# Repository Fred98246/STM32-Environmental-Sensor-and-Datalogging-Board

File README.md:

# Custom STM32 Environmental Sensor & Datalogging Board

## Project Overview
This repository contains the complete design files and source code for a custom, battery-powered STM32 microcontroller board designed for environmental monitoring and data logging. Measuring at a compact 40 x 58 mm, the board features integrated temperature, humidity, and ambient light sensors, alongside an SD card slot for local data storage. It includes a complete Li-Ion power management system with USB-C charging, load sharing, and battery protection. 

The user interface is driven by a rotary encoder and an external SPI display, making it suitable for standalone automated environments like humidity control or ambient monitoring.

## Repository Structure
*   **Hardware:** Contains the complete KiCad E.D.A. project files, including the schematic and the 4-layer PCB layout.
*   **Manufacturing:** Includes the generated Gerber files, Drill files, and sheets with the Bill of Materials (BOM) required for PCB fabrication and assembly.
*   **Firmware:** Contains the `STM32CubeMX` (`.ioc`) configuration file for peripheral initialization and the C/C++ code with the needed drivers.
*   **docs**: Contains component datasheets and a detailed Bill of Materials (BOM) spreadsheet

## Hardware Implementation Details

### Core Processing
*   **Microcontroller:** The board is powered by the STM32F103C8T6 ARM Cortex-M3 MCU.
*   **Clocking:** A 16MHz crystal oscillator (LFXTAL085871) is implemented to provide the precise clocking required for stable USB communication. 
*   **Debugging/Programming:** Connector for SWD programming, via ST-Link V2.

### Power Management
The power architecture is designed for safe, continuous operation whether plugged in or running on battery:
*   **Battery Charging:** Handled by the MCP73831/2 IC, drawing 5V from the USB-C port to charge a connected Li-Ion cell.
*   **Battery Protection:** An AP9101C IC, paired with dual ZXMN3B14F N-Channel MOSFETs, protects the battery from overcharge, overdischarge, and overcurrent scenarios.
*   **Load Sharing:** An AO3401A P-Channel MOSFET and an SS14 Schottky diode create a seamless load-sharing circuit. This ensures the system runs directly off USB power when plugged in, allowing the battery to charge optimally without system load interference.
*   **Regulation:** An AP2112K-3.3TRG1 LDO provides a stable 3.3V supply for the MCU and logic.

### Sensors & Interfaces
*   **Environmental Sensing:** Utilizes the SHT3x-DIS for high-precision temperature and humidity tracking via I2C.
*   **Light Sensing:** Incorporates the OPT3001DNPRQ1 ambient light sensor, also operating on the I2C bus.
*   **Storage:** A Molex 47219-2001 MicroSD card receptacle is routed via high-speed SPI for data logging in txt file.
*   **Connectivity:** USB-C port configured for USB 2.0 data and power. D3V3XA4B10LP TVS diode arrays are placed on both the USB data lines and the SD card lines to protect against electrostatic discharge (ESD).
*   USB-CDC Virtual COM Port Interface: Integrated full-speed USB communication between the STM32 and host PC, enabling real-time serial telemetry and diagnostic logging for hardware bring-up and physical fault isolation.
*   **User Input:** Hardware debounced rotary encoder footprint with integrated push-button functionality.

## Design Challenges & Signal Integrity
Designing this board within a 40x58mm footprint required careful attention to PCB stackup and signal routing:

*   **Component Footprints & Tolerances:** Extensive review of manufacturer datasheets was required to ensure precise footprint creation and component placement within the restricted 40x58mm board area.
*   **4-Layer Stackup:** To accommodate the component density and maintain strict signal integrity, a 4-layer PCB was utilized (Top Signal, Ground Plane, Power Plane, Bottom Signal). This continuous internal ground plane is critical for providing short return paths for high-frequency signals and minimizing electromagnetic interference (EMI). 
*   **USB Differential Routing:** The USB D+ and D- lines require 90-ohm differential impedance matching. The 4-layer stackup allowed for calculating precise trace widths and spacing over the internal ground plane to hit this impedance target, ensuring reliable USB enumeration and data transfer.
*   **MicroSD SPI Speeds:** Because SD card SPI operates at moderate speeds, it does not require strict impedance matching or length tuning. The 4-layer stackup provided the flexibility to route these signals easily through vias while maintaining a solid ground reference to minimize general EMI.
*   **Mixed-Signal Placement:** Analog sensor lines (I2C for SHT3x and OPT3001) are physically separated from high-speed digital traces (USB, SPI, and the 16MHz crystal) to prevent digital switching noise from coupling into the sensitive environmental readings.
*   **Firmware Architecture:** The C/C++ codebase leverages STM32 HAL libraries, structured with modular driver functions and a streamlined main loop to ensure non-blocking sensor reads and efficient peripheral management.

## Operational Flow & User Interface: 
The firmware is structured around an event-driven state machine that handles user interaction, data logging, and strict power efficiency:

*   **Startup & Menu Navigation:** The system is awakened by a physical press of the rotary encoder. The TFT display initializes and presents an interactive menu where the user can select to view Temperature, Humidity, or Ambient Light.
*   **Active Monitoring:** Upon selection, the screen continuously updates with real-time readings from the designated I2C sensor.
*   **Concurrent Datalogging & Telemetry:** While the system is awake, it automatically mounts the FATFS file system and appends the sensor readings to a `.txt` file on the MicroSD card at strict 10-second intervals. Simultaneously, this data is continuously broadcast over the USB-CDC COM port to a connected PC for live monitoring.
*   **Low-Power Sleep Mode:** To conserve battery, if the system detects no rotary encoder rotation or button clicks for 2 minutes, it automatically gracefully closes the SD card file, powers down the display, and puts the STM32 into a low-power `STOP` state. A subsequent button press triggers an EXTI hardware interrupt, waking the system back to full operation instantly.

## 🚀 Future Scope: Closed-Loop Automation
While currently operating as a standalone datalogger, this board was engineered to serve as the precision sensor node for future automated control systems. By linking the onboard environmental telemetry to external physical actuators (such as fans, humidifiers, or motorized blinds), the hardware will transition into a dynamic closed-loop control environment. 

The high-resolution empirical data currently gathered via the SD card and USB interface provides the foundation for mathematical system identification. This allows the physical environment's behavior to be accurately modeled in software like MATLAB, enabling the future calculation of transfer functions and the implementation of tuned PID or automated sequential control logic directly onto the STM32.

*   **Schematic**:

* **PCB**:

* **3D View**:

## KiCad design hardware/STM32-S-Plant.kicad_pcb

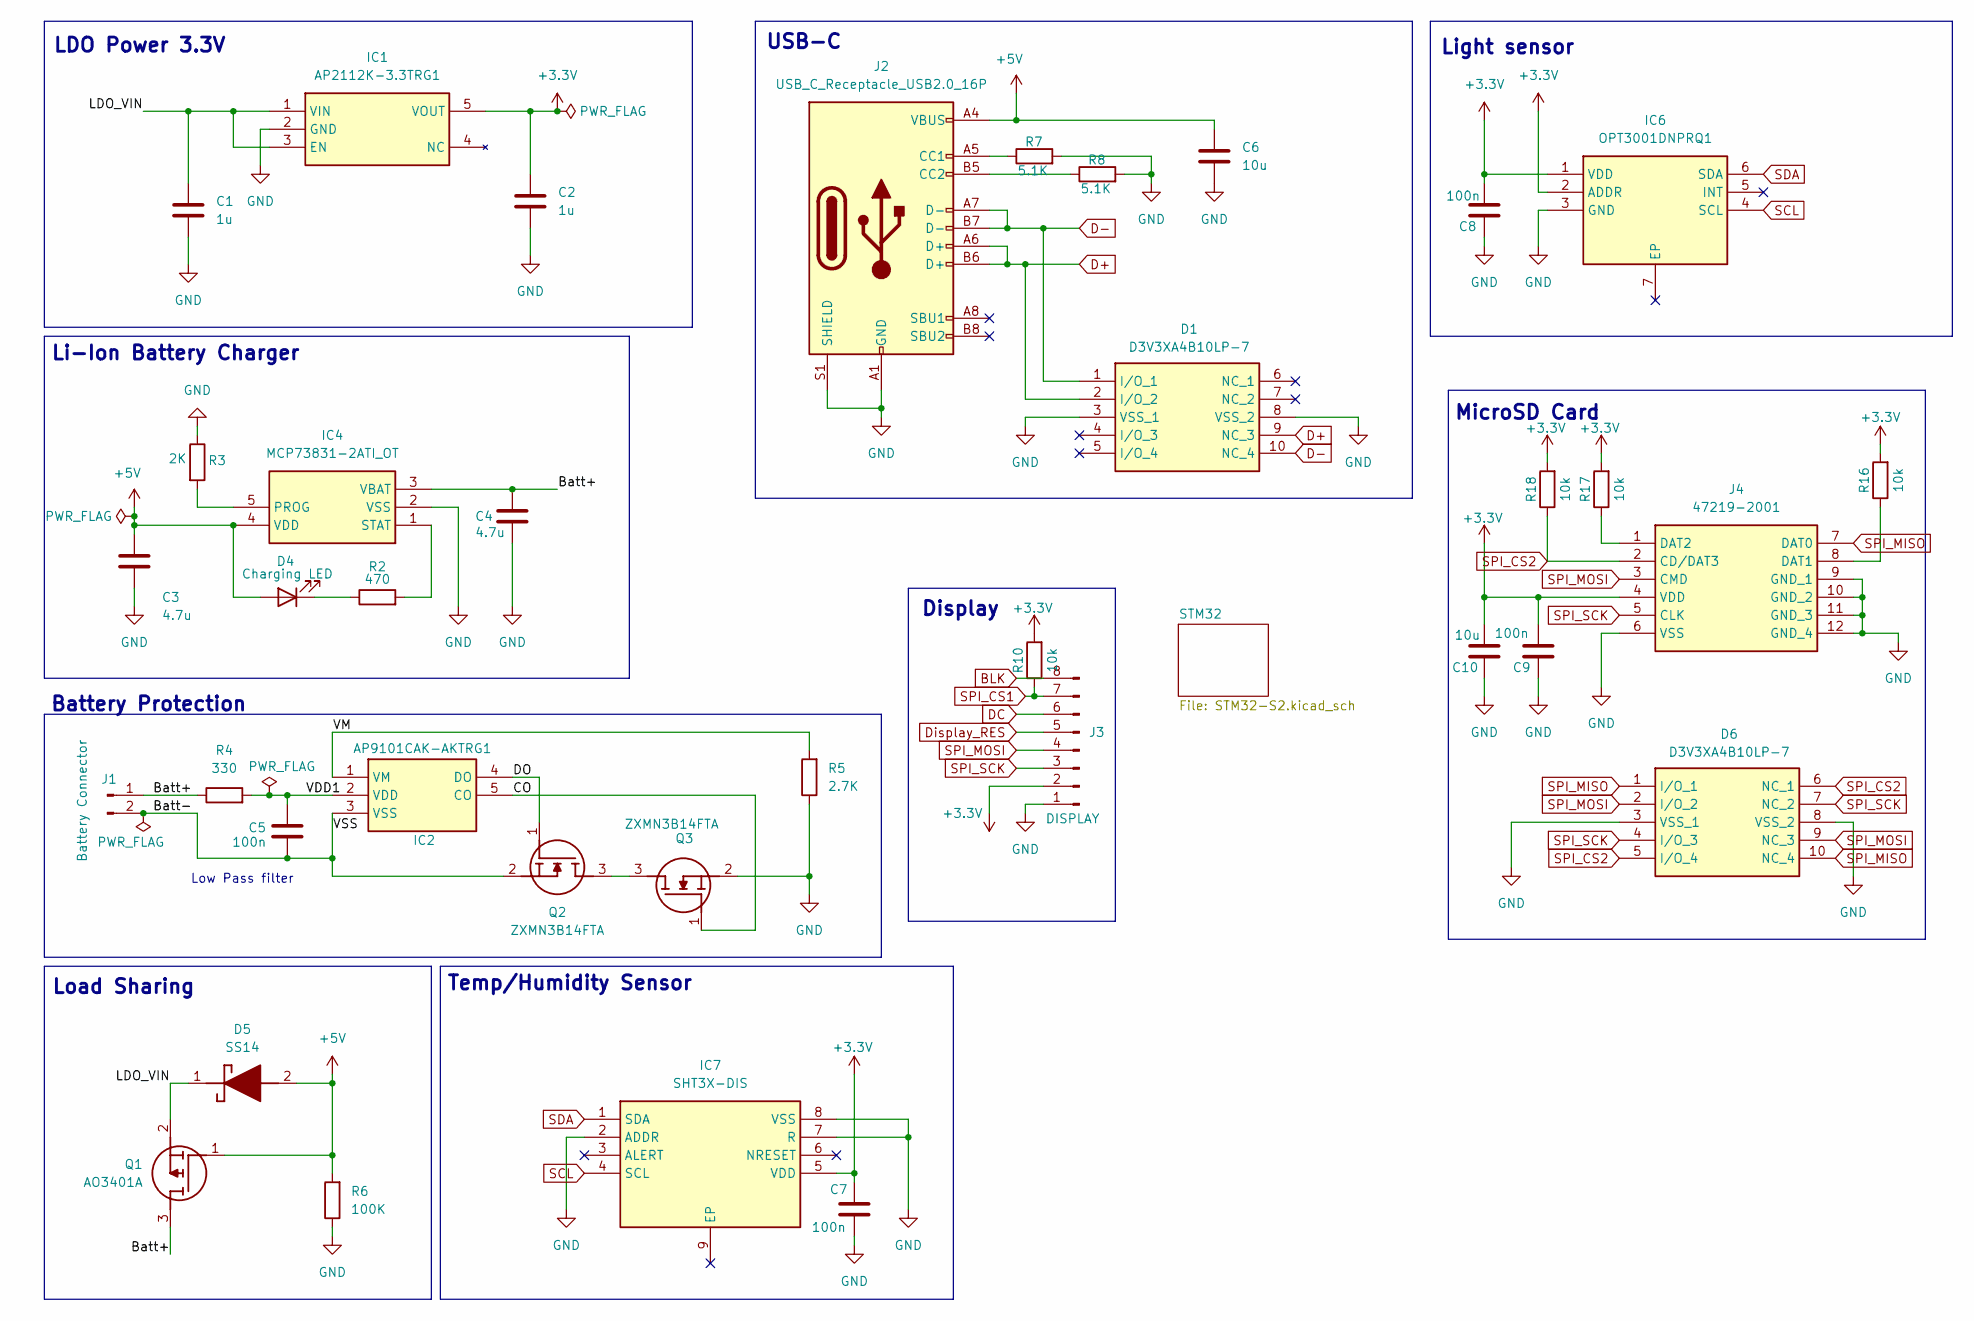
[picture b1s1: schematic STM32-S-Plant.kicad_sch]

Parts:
C1, C2: 1u; C_0402_1005Metric
C3, C4: 4.7u; C_0805_2012Metric
C5, C7, C8, C9: 100n; C_0402_1005Metric
C6, C10: 10u; C_0805_2012Metric
D1, D6: D3V3XA4B10LP-7; D3V3XA4B10LP7; Manufacturer_Part_Number D3V3XA4B10LP-7; Mouser Part Number 621-D3V3XA4B10LP-7
D4: Charging LED; C_0603_1608Metric
D5: SS14; DIOM5026X230N; Manufacturer_Part_Number SS14
IC1: AP2112K-3.3TRG1; SOT95P270X145-5N; Manufacturer_Part_Number AP2112K-3.3TRG1; Mouser Part Number 621-AP2112K-3.3TRG1
IC2: AP9101CAK-AKTRG1; SOT95P270X145-5N; Manufacturer_Part_Number AP9101CAK-AKTRG1; Mouser Part Number 621-AP9101CAK-AKTRG1
IC4: MCP73831-2ATI_OT; SOT95P270X145-5N; Manufacturer_Part_Number MCP73831-2ATI/OT
IC6: OPT3001DNPRQ1; SON65P200X200X65-7N-D; Manufacturer_Part_Number OPT3001DNPRQ1; Mouser Part Number 595-OPT3001DNPRQ1
IC7: SHT3X-DIS; SON50P250X250X100-9N-D; Manufacturer_Part_Number SHT3X-DIS
J1: Battery Connector; PinHeader_1x02_P2.54mm_Vertical
J2: USB_C_Receptacle_USB2.0_16P; USB_C_Receptacle_GCT_USB4105-xx-A_16P_TopMnt_Horizontal
J3: DISPLAY; PinHeader_1x08_P2.54mm_Vertical
J4: 47219-2001; 472192001; Manufacturer_Part_Number 47219-2001; Mouser Part Number 538-47219-2001
Q1: AO3401A; SOT95P280X125-3N; Manufacturer_Part_Number AO3401A
Q2, Q3: ZXMN3B14FTA; Manufacturer_Part_Number ZXMN3B14FTA; Mouser Part Number 522-ZXMN3B14FTA
R2: 470; R_0603_1608Metric
R3: 2K; R_0603_1608Metric
R4: 330; R_0603_1608Metric
R5: 2.7K; R_0603_1608Metric
R6: 100K; R_0603_1608Metric
R7, R8: 5.1K; R_0603_1608Metric
R10, R16, R17, R18: 10k; R_0603_1608Metric

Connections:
+3.3V: C2.1, C7.1, C8.2, C9.2, C10.2, IC1.5 (VOUT), IC6.1 (VDD), IC6.2 (ADDR), IC7.5 (VDD), J3.2, J4.4 (VDD), R10.2, R16.2, R17.2, R18.2; also elsewhere on the board
+5V: C3.1, C6.1, D4.2 (A), D5.2 (A), IC4.4 (VDD), J2.A4 (VBUS), J2.A9 (VBUS), J2.B4 (VBUS), J2.B9 (VBUS), Q1.1 (G), R6.2
/Batt+: C4.1, IC4.3 (VBAT), J1.1, Q1.3 (D), R4.1
/Batt-: C5.2, IC2.3 (VSS), J1.2, Q2.2 (S)
/CO: IC2.5 (CO), Q3.1 (G)
/DO: IC2.4 (DO), Q2.1 (G)
/LDO_VIN: C1.1, D5.1 (K), IC1.1 (VIN), IC1.3 (EN), Q1.2 (S)
/VDD1: C5.1, IC2.2 (VDD), R4.2
/VM: IC2.1 (VM), R5.2
BLK: J3.8; also elsewhere on the board
D+: D1.2 (I/O_2), D1.9 (NC_3), J2.A6 (D+), J2.B6 (D+); also elsewhere on the board
D-: D1.1 (I/O_1), D1.10 (NC_4), J2.A7 (D-), J2.B7 (D-); also elsewhere on the board
DC: J3.6; also elsewhere on the board
Display_RES: J3.5; also elsewhere on the board
GND: C1.2, C2.2, C3.2, C4.2, C6.2, C7.2, C8.1, C9.1, C10.1, D1.3 (VSS_1), D1.8 (VSS_2), D6.3 (VSS_1), D6.8 (VSS_2), IC1.2 (GND), IC4.2 (VSS), IC6.3 (GND), IC7.2 (ADDR), IC7.7 (R), IC7.8 (VSS), J2.A1 (GND), J2.A12 (GND), J2.B1 (GND), J2.B12 (GND), J2.S1 (SHIELD), J3.1, J4.6 (VSS), J4.9 (GND_1), J4.10 (GND_2), J4.11 (GND_3), J4.12 (GND_4), Q3.2 (S), R3.1, R5.1, R6.1, R7.2, R8.2; also elsewhere on the board
unnamed: D4.1 (K), R2.1
unnamed: IC4.5 (PROG), R3.2
unnamed: IC4.1 (STAT), R2.2
unnamed: J2.A5 (CC1), R7.1
unnamed: J2.B5 (CC2), R8.1
unnamed: J4.8 (DAT1), R16.1
unnamed: J4.1 (DAT2), R17.1
unnamed: Q2.3 (D), Q3.3 (D)
SCL: IC6.4 (SCL), IC7.4 (SCL); also elsewhere on the board
SDA: IC6.6 (SDA), IC7.1 (SDA); also elsewhere on the board
SPI_CS1: J3.7, R10.1; also elsewhere on the board
SPI_CS2: D6.5 (I/O_4), D6.6 (NC_1), J4.2 (CD/DAT3), R18.1; also elsewhere on the board
SPI_MISO: D6.1 (I/O_1), D6.10 (NC_4), J4.7 (DAT0); also elsewhere on the board
SPI_MOSI: D6.2 (I/O_2), D6.9 (NC_3), J3.4, J4.3 (CMD); also elsewhere on the board
SPI_SCK: D6.4 (I/O_3), D6.7 (NC_2), J3.3, J4.5 (CLK); also elsewhere on the board

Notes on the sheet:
Light sensor
Display
USB-C
Low Pass filter
Load Sharing
MicroSD Card
Battery Protection
LDO Power 3.3V
Li-Ion Battery Charger
Temp/Humidity Sensor

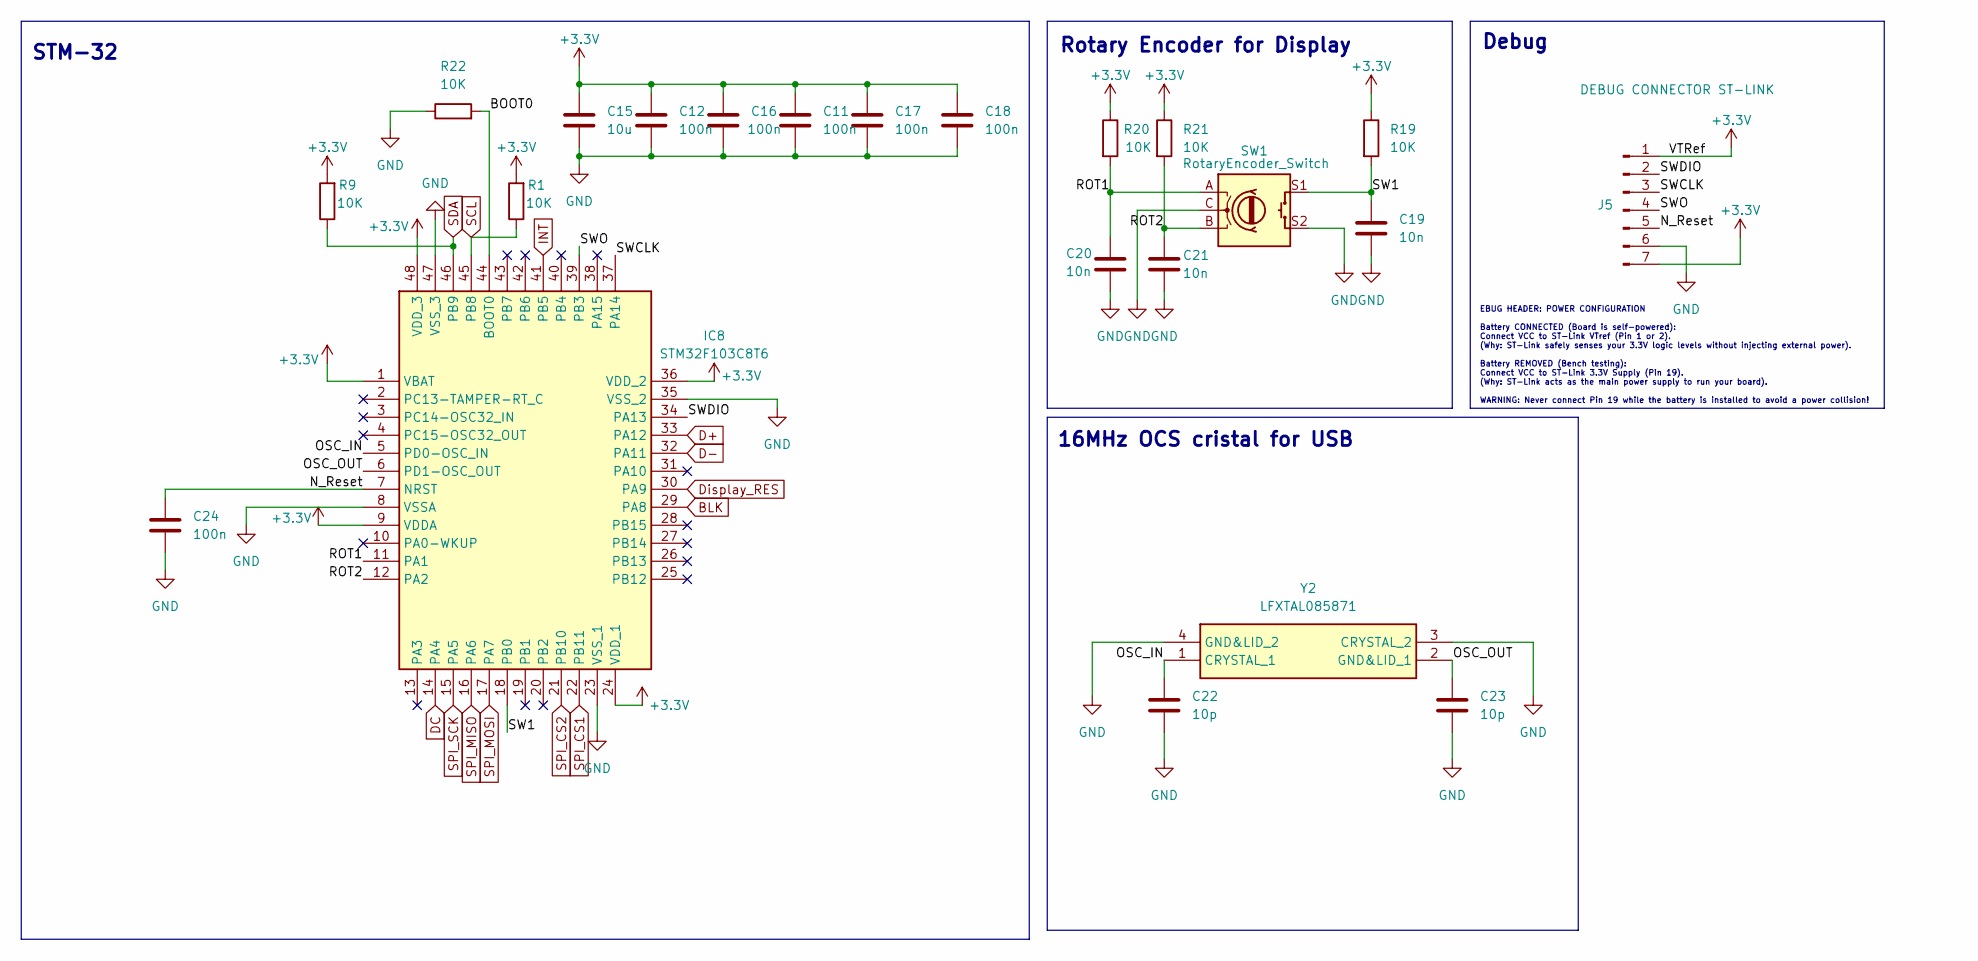
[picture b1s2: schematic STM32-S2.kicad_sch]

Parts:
C11, C12, C16, C17, C18, C24: 100n; C_0402_1005Metric
C15: 10u; C_0805_2012Metric
C19, C20, C21: 10n; C_0402_1005Metric
C22, C23: 10p; C_0402_1005Metric
IC8: STM32F103C8T6; QFP50P900X900X160-48N; Manufacturer_Part_Number STM32F103C8T6; Mouser Part Number 511-STM32F103C8T6
J5: DEBUG CONNECTOR ST-LINK; PinHeader_1x07_P2.54mm_Vertical
R1, R9, R19, R20, R21, R22: 10K; R_0603_1608Metric
SW1: RotaryEncoder_Switch; RotaryEncoder_Alps_EC11E-Switch_Vertical_H20mm_MountingHoles
Y2: LFXTAL085871; Manufacturer_Part_Number LFXTAL085871

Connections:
+3.3V: C11.1, C12.1, C15.1, C16.1, C17.1, C18.1, IC8.1 (VBAT), IC8.9 (VDDA), IC8.24 (VDD_1), IC8.36 (VDD_2), IC8.48 (VDD_3), J5.1, J5.7, R1.2, R9.2, R19.1, R20.1, R21.1; also elsewhere on the board
/STM32/BOOT0: IC8.44 (BOOT0), R22.2
/STM32/N_Reset: C24.1, IC8.7 (NRST), J5.5
/STM32/OSC_IN: C22.1, IC8.5 (PD0-OSC_IN), Y2.1 (CRYSTAL_1)
/STM32/OSC_OUT: C23.1, IC8.6 (PD1-OSC_OUT), Y2.2 (GND&LID_1)
/STM32/ROT1: C20.1, IC8.11 (PA1), R20.2, SW1.A
/STM32/ROT2: C21.1, IC8.12 (PA2), R21.2, SW1.B
/STM32/SW1: C19.1, IC8.18 (PB0), R19.2, SW1.S1
/STM32/SWCLK: IC8.37 (PA14), J5.3
/STM32/SWDIO: IC8.34 (PA13), J5.2
/STM32/SWO: IC8.39 (PB3), J5.4
BLK: IC8.29 (PA8); also elsewhere on the board
D+: IC8.33 (PA12); also elsewhere on the board
D-: IC8.32 (PA11); also elsewhere on the board
DC: IC8.14 (PA4); also elsewhere on the board
Display_RES: IC8.30 (PA9); also elsewhere on the board
GND: C11.2, C12.2, C15.2, C16.2, C17.2, C18.2, C19.2, C20.2, C21.2, C22.2, C23.2, C24.2, IC8.8 (VSSA), IC8.23 (VSS_1), IC8.35 (VSS_2), IC8.47 (VSS_3), J5.6, R22.1, SW1.C, SW1.S2, Y2.3 (CRYSTAL_2), Y2.4 (GND&LID_2); also elsewhere on the board
INT: IC8.41 (PB5)
SCL: IC8.45 (PB8), R1.1; also elsewhere on the board
SDA: IC8.46 (PB9), R9.1; also elsewhere on the board
SPI_CS1: IC8.22 (PB11); also elsewhere on the board
SPI_CS2: IC8.21 (PB10); also elsewhere on the board
SPI_MISO: IC8.16 (PA6); also elsewhere on the board
SPI_MOSI: IC8.17 (PA7); also elsewhere on the board
SPI_SCK: IC8.15 (PA5); also elsewhere on the board

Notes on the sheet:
Debug
STM-32
Rotary Encoder for Display
16MHz OCS cristal for USB
EBUG HEADER: POWER CONFIGURATION Battery CONNECTED (Board is self-powered): Connect VCC to ST-Link VTref (Pin 1 or 2). (Why: ST-Link safely senses your 3.3V logic levels without injecting external power). Battery REMOVED (Bench testing): Connect VCC to ST-Link 3.3V Supply (Pin 19). (Why: ST-Link ac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

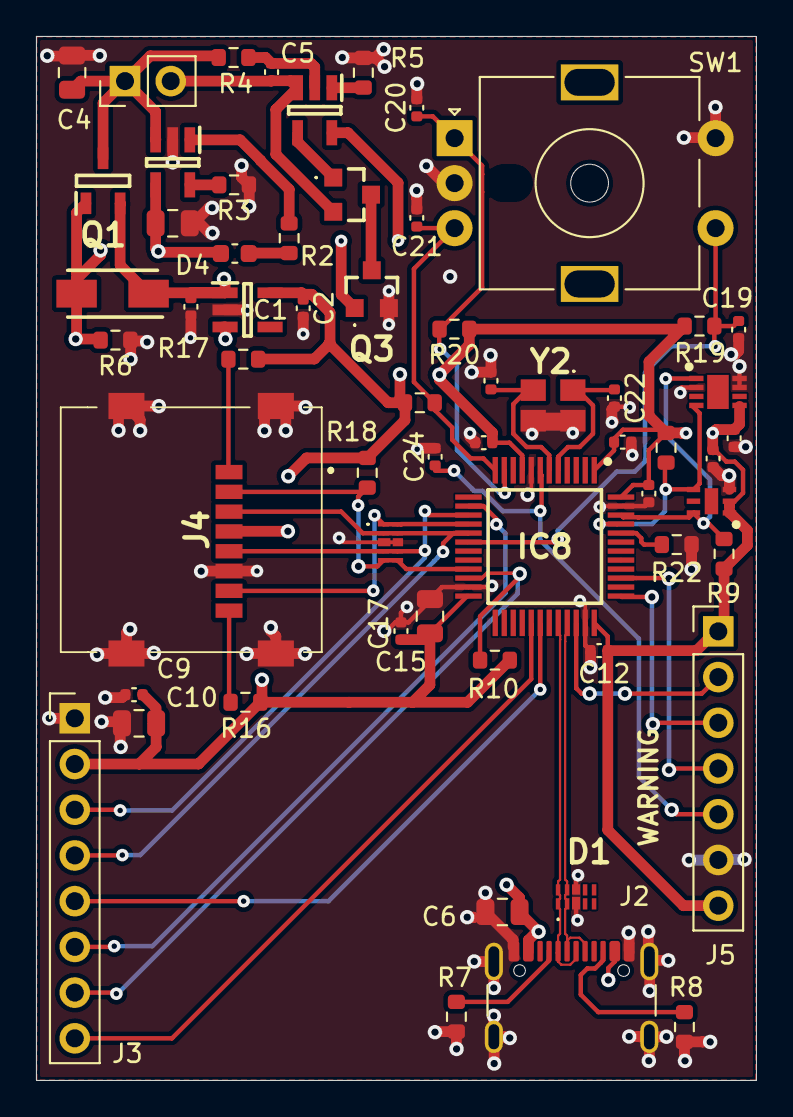
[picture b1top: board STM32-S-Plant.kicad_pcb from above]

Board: 4 copper layers, 40.0 x 58.0 mm, 59 parts (0 on the bottom side), 40 nets.

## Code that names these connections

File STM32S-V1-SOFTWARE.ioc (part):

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Mcu.Name=STM32F103C(8-B)Tx
Mcu.Package=LQFP48
Mcu.UserName=STM32F103C8Tx
PA1.GPIOParameters=GPIO_Label,GPIO_ModeDefaultEXTI
PA1.GPIO_Label=ROT1
PA1.GPIO_ModeDefaultEXTI=GPIO_MODE_IT_RISING_FALLING
PA1.Signal=GPXTI1
PA11.Mode=Device
PA11.Signal=USB_DM
PA12.Mode=Device
PA12.Signal=USB_DP
PA13.Mode=Serial_Wire
PA13.Signal=SYS_JTMS-SWDIO
PA14.Mode=Serial_Wire
PA14.Signal=SYS_JTCK-SWCLK
PA2.GPIOParameters=GPIO_Label,GPIO_ModeDefaultEXTI
PA2.GPIO_Label=ROT2
PA2.GPIO_ModeDefaultEXTI=GPIO_MODE_IT_RISING_FALLING
PA2.Signal=GPXTI2
PA4.GPIOParameters=GPIO_Speed,PinState,GPIO_Label
PA4.GPIO_Label=DC
PA4.GPIO_Speed=GPIO_SPEED_FREQ_HIGH
PA4.PinState=GPIO_PIN_RESET
PA4.Signal=GPIO_Output
PA5.Mode=Full_Duplex_Master
PA5.Signal=SPI1_SCK
PA6.Mode=Full_Duplex_Master
PA6.Signal=SPI1_MISO
PA7.Mode=Full_Duplex_Master
PA7.Signal=SPI1_MOSI
PA8.GPIOParameters=GPIO_Label
PA8.GPIO_Label=BLK
PA8.Signal=GPIO_Output
PA9.GPIOParameters=GPIO_Speed,PinState,GPIO_Label
PA9.GPIO_Label=Display_RES
PA9.GPIO_Speed=GPIO_SPEED_FREQ_LOW
PA9.PinState=GPIO_PIN_SET
PA9.Signal=GPIO_Output
PB0.GPIOParameters=GPIO_Label,GPIO_ModeDefaultEXTI
PB0.GPIO_Label=SW1
PB0.GPIO_ModeDefaultEXTI=GPIO_MODE_IT_FALLING
PB0.Signal=GPXTI0
PB10.GPIOParameters=GPIO_Speed,PinState,GPIO_Label
PB10.GPIO_Label=SPI_CS2
PB10.GPIO_Speed=GPIO_SPEED_FREQ_HIGH
PB10.PinState=GPIO_PIN_SET
PB10.Signal=GPIO_Output
PB11.GPIOParameters=GPIO_Speed,PinState,GPIO_Label
PB11.GPIO_Label=SPI_CS1
PB11.GPIO_Speed=GPIO_SPEED_FREQ_HIGH
PB11.PinState=GPIO_PIN_SET
PB11.Signal=GPIO_Output
PB3.Signal=SYS_JTDO-TRACESWO
PB8.Mode=I2C
PB8.Signal=I2C1_SCL
PB9.Mode=I2C
PB9.Signal=I2C1_SDA
PD0-OSC_IN.Mode=HSE-External-Oscillator
PD0-OSC_IN.Signal=RCC_OSC_IN
PD1-OSC_OUT.Mode=HSE-External-Oscillator
PD1-OSC_OUT.Signal=RCC_OSC_OUT
RCC.HSE_VALUE=16000000
RCC.SYSCLKFreq_VALUE=16000000
RCC.SYSCLKSource=RCC_SYSCLKSOURCE_HSE
board=custom
